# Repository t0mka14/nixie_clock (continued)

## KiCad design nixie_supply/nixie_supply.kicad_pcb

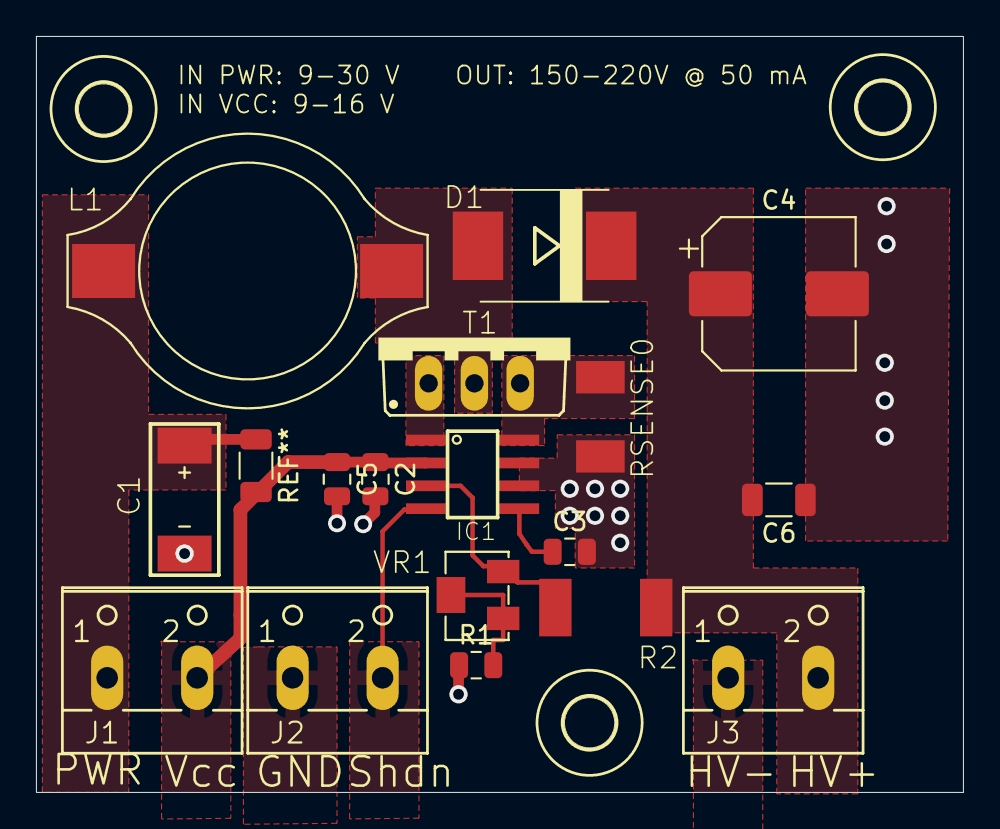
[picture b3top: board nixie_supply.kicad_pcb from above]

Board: 2 copper layers, 51.5 x 42.0 mm, 20 parts (0 on the bottom side), 11 nets.

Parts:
C1: 100uF,35V; C-EIA-7343
C2, C3: 100n; C_0805_2012Metric
C4: 4u7,250V; CP_Elec_8x10
C5: 10uF,25V; C_0805_2012Metric
C6: 100n,250V; C_1206_3216Metric
D1: ES2F; SMC
IC1: MAX1771ESA; SO-8
J1, J2, J3: SCREW-2-02
L1: 100uH; L-B82479
R1: 10K; C_0805_2012Metric
R2: 1M5; R2512
RSENSE0: 0R050; R2010
T1: IRF644PBF; TO220BV
U$2, U$3, U$4: 2,8
VR1: 5K; BOURNS-3214W

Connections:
DGND: C1.-, C2.2, C3.2, C4.2, C5.2, C6.1, IC1.6, IC1.7, J2.1, J3.1, R1.1, RSENSE0.1
EXT: IC1.1, T1.G
unnamed: IC1.8, RSENSE0.2, T1.S
unnamed: R1.2, VR1.1, VR1.2
unnamed: IC1.3, R2.1, VR1.3
unnamed: D1.A, L1.P$2, T1.D
unnamed: C3.1, IC1.5
PWR: C1.+, J1.1, L1.P$1
SHDN: IC1.4, J2.2
VCC: C2.1, C5.1, IC1.2, J1.2
VOUT: C4.1, C6.2, D1.C, J3.2, R2.2

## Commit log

2025-03-10 init commit
2025-04-12 edit Readme.md
2025-04-13 Add files via upload
    added image
2025-04-13 added images
